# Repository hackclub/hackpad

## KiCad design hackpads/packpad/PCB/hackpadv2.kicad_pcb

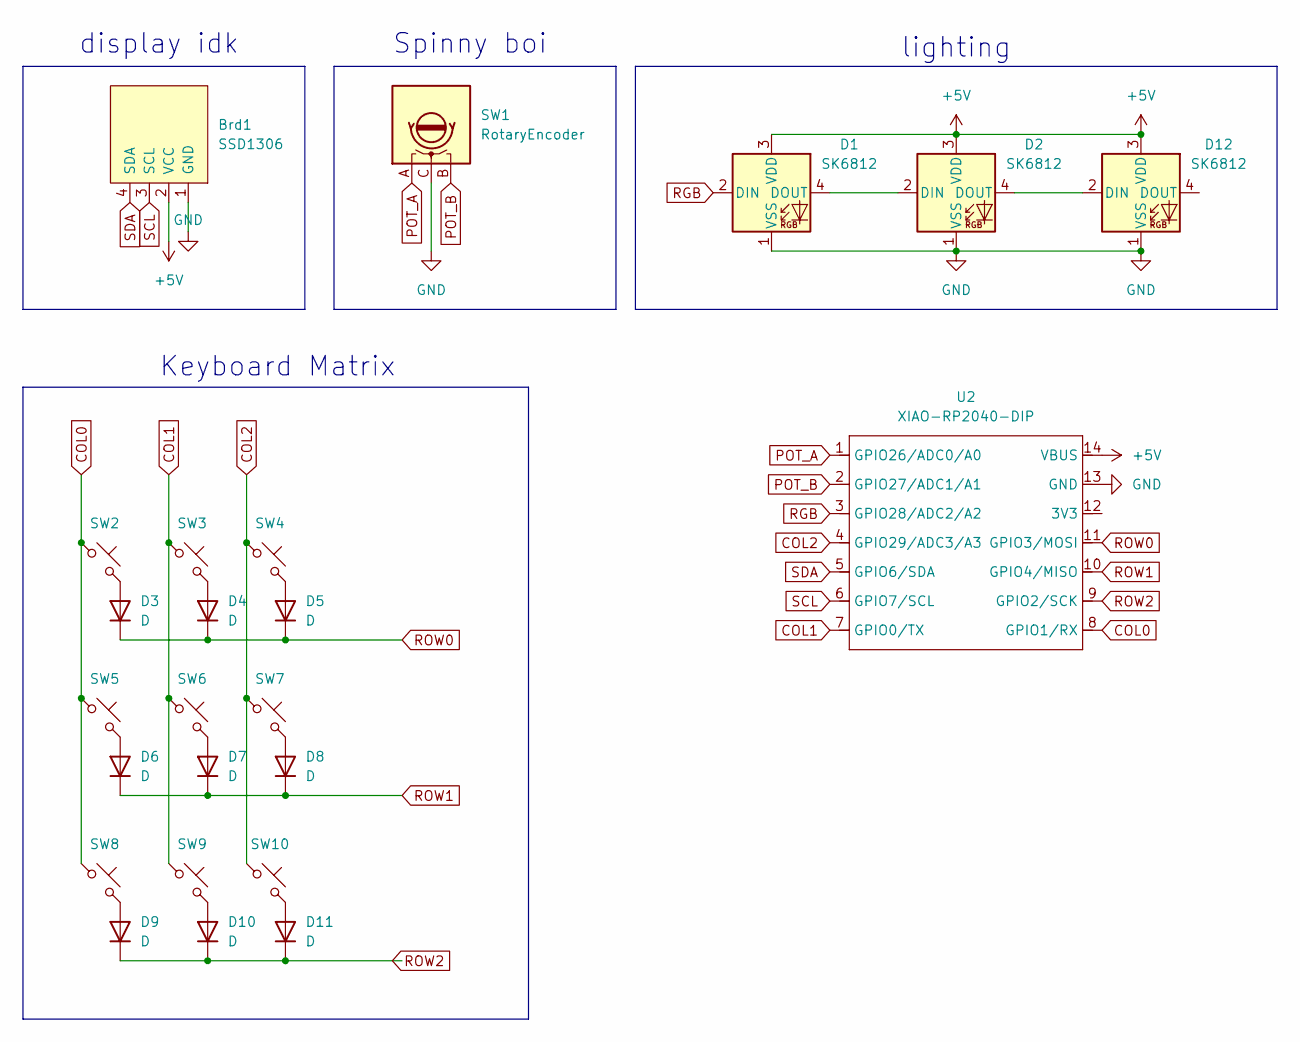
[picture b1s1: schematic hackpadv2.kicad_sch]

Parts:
Brd1: SSD1306
D1, D2, D12: SK6812; LED_SK6812_PLCC4_5.0x5.0mm_P3.2mm
D3, D4, D5, D6, D7, D8, D9, D10, D11: D; D_DO-35_SOD27_P7.62mm_Horizontal
SW1: RotaryEncoder; RotaryEncoder_Alps_EC11E-Switch_Vertical_H20mm
SW2, SW3, SW4, SW5, SW6, SW7, SW8, SW9, SW10: SW_Push_45deg; SW_Cherry_MX_1.00u_PCB
U2: XIAO-RP2040-DIP

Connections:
+5V: Brd1.2 (VCC), D1.3 (VDD), D2.3 (VDD), D12.3 (VDD), U2.14 (VBUS); also elsewhere on the board
COL0: SW2.1, SW5.1, SW8.1, U2.8 (GPIO1/RX)
COL1: SW3.1, SW6.1, SW9.1, U2.7 (GPIO0/TX)
COL2: SW4.1, SW7.1, SW10.1, U2.4 (GPIO29/ADC3/A3)
GND: Brd1.1 (GND), D1.1 (VSS), D2.1 (VSS), D12.1 (VSS), SW1.C, U2.13 (GND); also elsewhere on the board
unnamed: D1.4 (DOUT), D2.2 (DIN)
unnamed: D3.2 (A), SW2.2
unnamed: D4.2 (A), SW3.2
unnamed: D5.2 (A), SW4.2
unnamed: D6.2 (A), SW5.2
unnamed: D7.2 (A), SW6.2
unnamed: D8.2 (A), SW7.2
unnamed: D9.2 (A), SW8.2
unnamed: D10.2 (A), SW9.2
unnamed: D11.2 (A), SW10.2
unnamed: D2.4 (DOUT), D12.2 (DIN)
POT_A: SW1.A, U2.1 (GPIO26/ADC0/A0)
POT_B: SW1.B, U2.2 (GPIO27/ADC1/A1)
RGB: D1.2 (DIN), U2.3 (GPIO28/ADC2/A2)
ROW0: D3.1 (K), D4.1 (K), D5.1 (K), U2.11 (GPIO3/MOSI)
ROW1: D6.1 (K), D7.1 (K), D8.1 (K), U2.10 (GPIO4/MISO)
ROW2: D9.1 (K), D10.1 (K), D11.1 (K), U2.9 (GPIO2/SCK)
SCL: Brd1.3 (SCL), U2.6 (GPIO7/SCL); also elsewhere on the board
SDA: Brd1.4 (SDA), U2.5 (GPIO6/SDA); also elsewhere on the board

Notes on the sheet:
lighting
display idk
Keyboard Matrix
Spinny boi

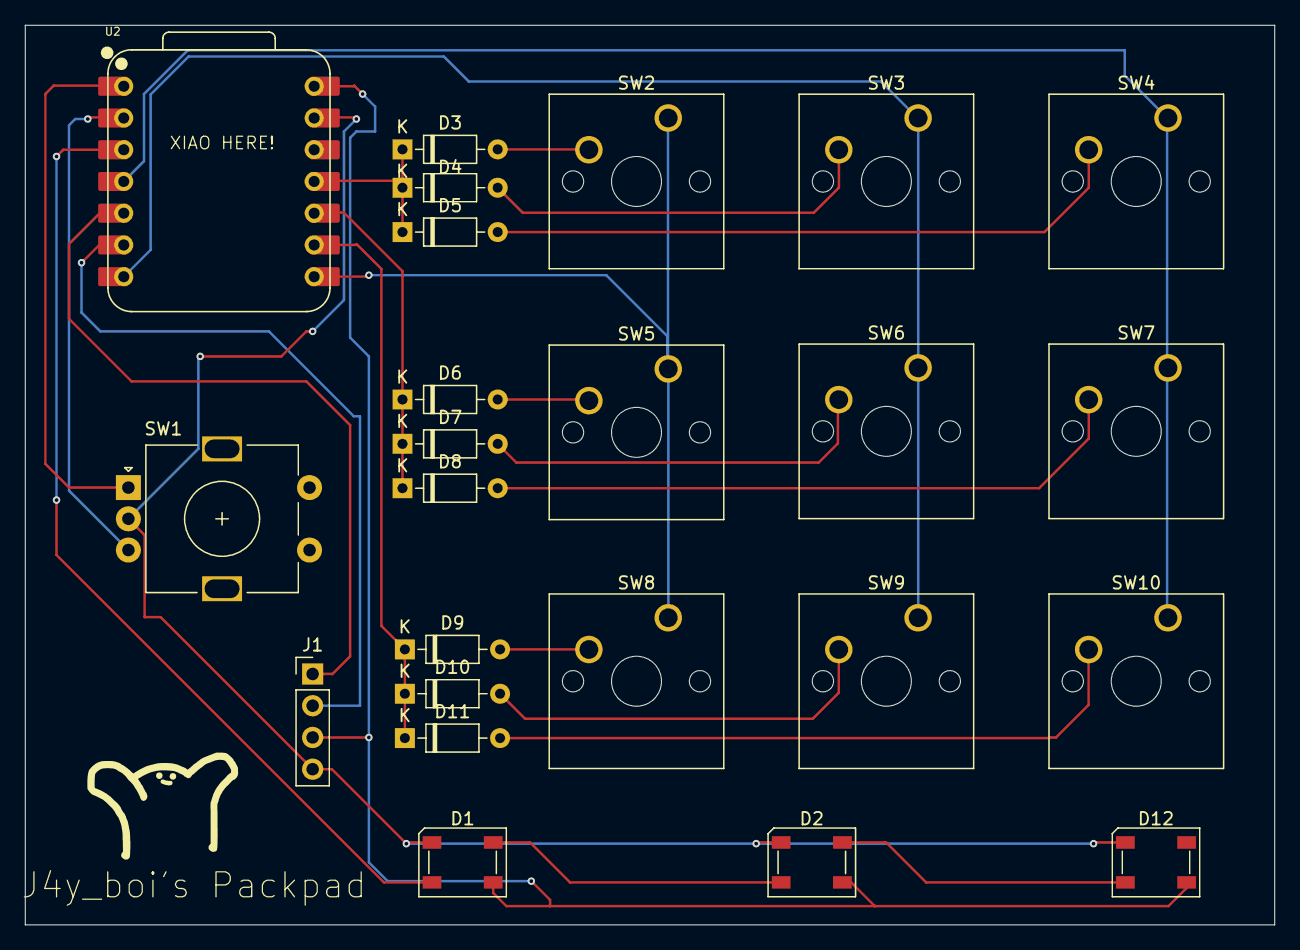
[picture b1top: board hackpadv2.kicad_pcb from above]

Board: 2 copper layers, 100.0 x 72.0 mm, 24 parts (0 on the bottom side), 24 nets.

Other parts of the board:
J1: OLED_DISPLAY; PinHeader_1x04_P2.54mm_Vertical

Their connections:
+5V: J1.3; also elsewhere on the board
GND: J1.4; also elsewhere on the board
SCL: J1.2; also elsewhere on the board
SDA: J1.1; also elsewhere on the board

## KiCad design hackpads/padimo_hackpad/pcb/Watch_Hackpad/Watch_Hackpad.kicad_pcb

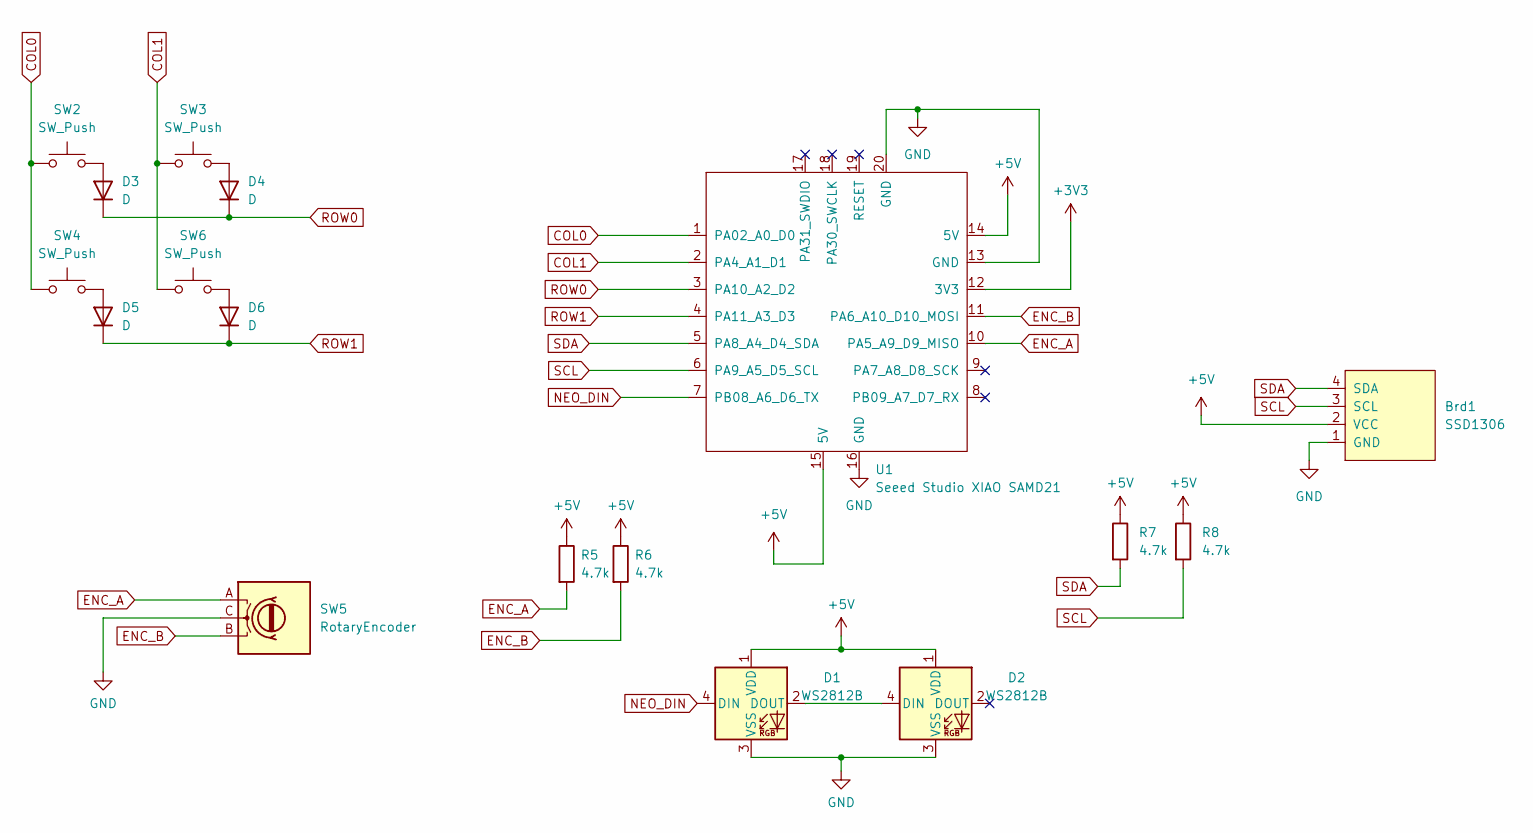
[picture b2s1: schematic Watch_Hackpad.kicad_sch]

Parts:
Brd1: SSD1306; SSD1306_128x64
D1, D2: WS2812B; LED_WS2812B_PLCC4_5.0x5.0mm_P3.2mm
D3, D4, D5, D6: D; D_DO-35_SOD27_P7.62mm_Horizontal
R5, R6, R7, R8: 4.7k; CF14JT4K70
SW2, SW3, SW4, SW6: SW_Push; SW_Cherry_MX_1.00u_PCB
SW5: RotaryEncoder; RotaryEncoder_Alps_EC11E-Switch_Vertical_H20mm
U1: Seeed Studio XIAO SAMD21; XIAO-SAMD21-RP2040-14P-2.54-21X17.8MM (Seeeduino XIAO)

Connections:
+3V3: U1.12 (3V3)
+5V: Brd1.2 (VCC), D1.1 (VDD), D2.1 (VDD), R5.1, R6.1, R7.1, R8.1, U1.14 (5V), U1.15 (5V)
COL0: SW2.1, SW4.1, U1.1 (PA02_A0_D0)
COL1: SW3.1, SW6.1, U1.2 (PA4_A1_D1)
ENC_A: R5.2, SW5.A, U1.10 (PA5_A9_D9_MISO)
ENC_B: R6.2, SW5.B, U1.11 (PA6_A10_D10_MOSI)
GND: Brd1.1 (GND), D1.3 (VSS), D2.3 (VSS), SW5.C, U1.13 (GND), U1.16 (GND), U1.20 (GND)
NEO_DIN: D1.4 (DIN), U1.7 (PB08_A6_D6_TX)
unnamed: D1.2 (DOUT), D2.4 (DIN)
unnamed: D3.2 (A), SW2.2
unnamed: D4.2 (A), SW3.2
unnamed: D5.2 (A), SW4.2
unnamed: D6.2 (A), SW6.2
ROW0: D3.1 (K), D4.1 (K), U1.3 (PA10_A2_D2)
ROW1: D5.1 (K), D6.1 (K), U1.4 (PA11_A3_D3)
SCL: Brd1.3 (SCL), R8.2, U1.6 (PA9_A5_D5_SCL)
SDA: Brd1.4 (SDA), R7.2, U1.5 (PA8_A4_D4_SDA)

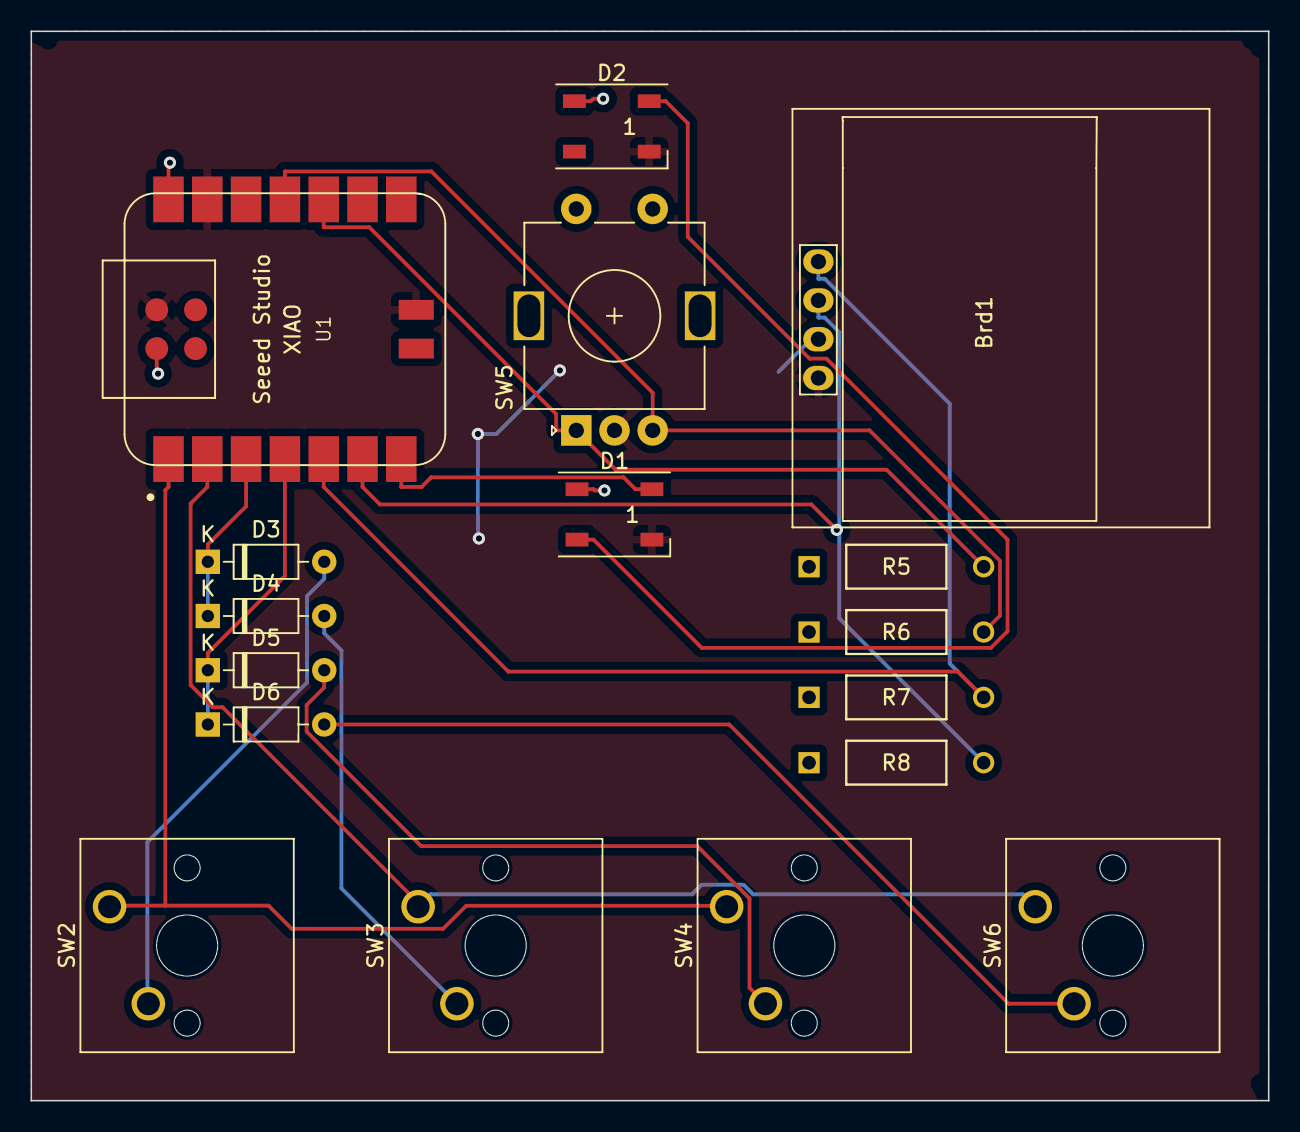
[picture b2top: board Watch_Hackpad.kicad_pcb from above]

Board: 2 copper layers, 81.0 x 70.0 mm, 17 parts (0 on the bottom side), 16 nets.

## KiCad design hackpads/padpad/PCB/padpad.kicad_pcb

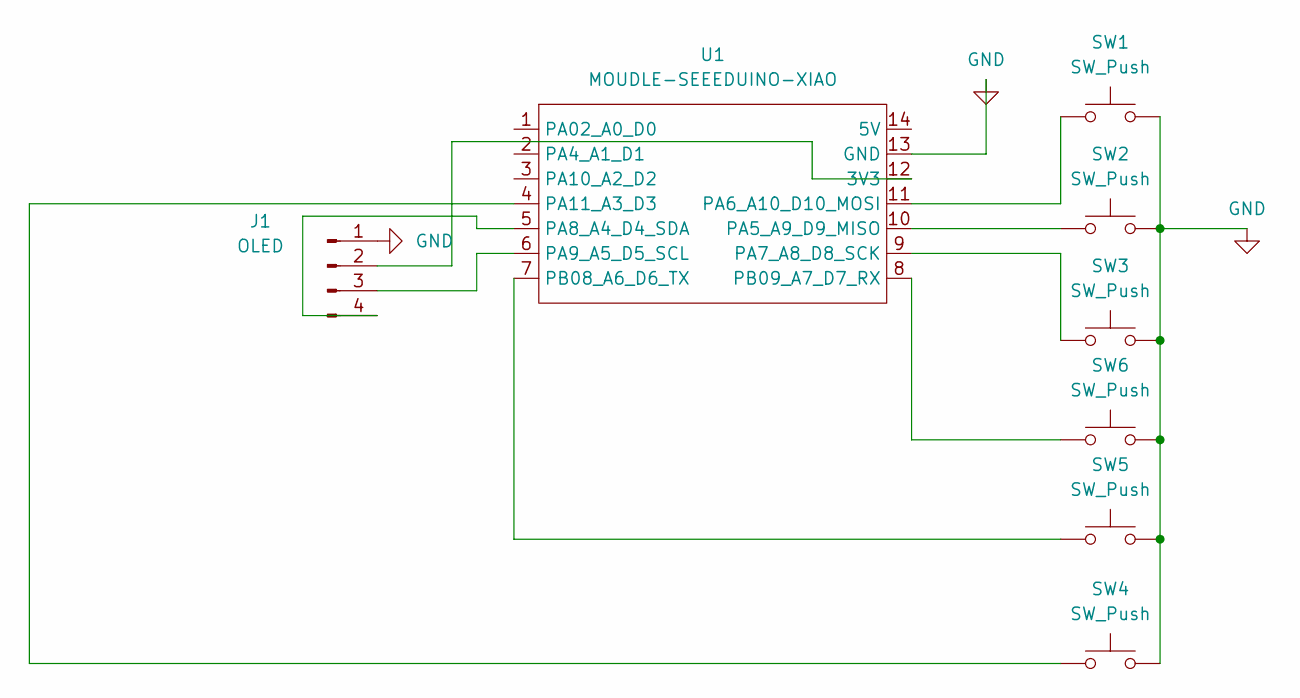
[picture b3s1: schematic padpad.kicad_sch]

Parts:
J1: OLED; SSD1306-0.91-OLED-4pin-128x32
SW1, SW2, SW3, SW4, SW5, SW6: SW_Push; SW_Cherry_MX_1.00u_PCB
U1: MOUDLE-SEEEDUINO-XIAO; XIAO-Generic-Hybrid-14P-2.54-21X17.8MM

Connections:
GND: J1.1, SW1.2, SW2.2, SW3.2, SW4.2, SW5.2, SW6.2, U1.13 (GND)
unnamed: J1.2, U1.12 (3V3)
unnamed: J1.3, U1.6 (PA9_A5_D5_SCL)
unnamed: J1.4, U1.5 (PA8_A4_D4_SDA)
unnamed: SW2.1, U1.10 (PA5_A9_D9_MISO)
unnamed: SW1.1, U1.11 (PA6_A10_D10_MOSI)
unnamed: SW3.1, U1.9 (PA7_A8_D8_SCK)
unnamed: SW4.1, U1.4 (PA11_A3_D3)
unnamed: SW5.1, U1.7 (PB08_A6_D6_TX)
unnamed: SW6.1, U1.8 (PB09_A7_D7_RX)

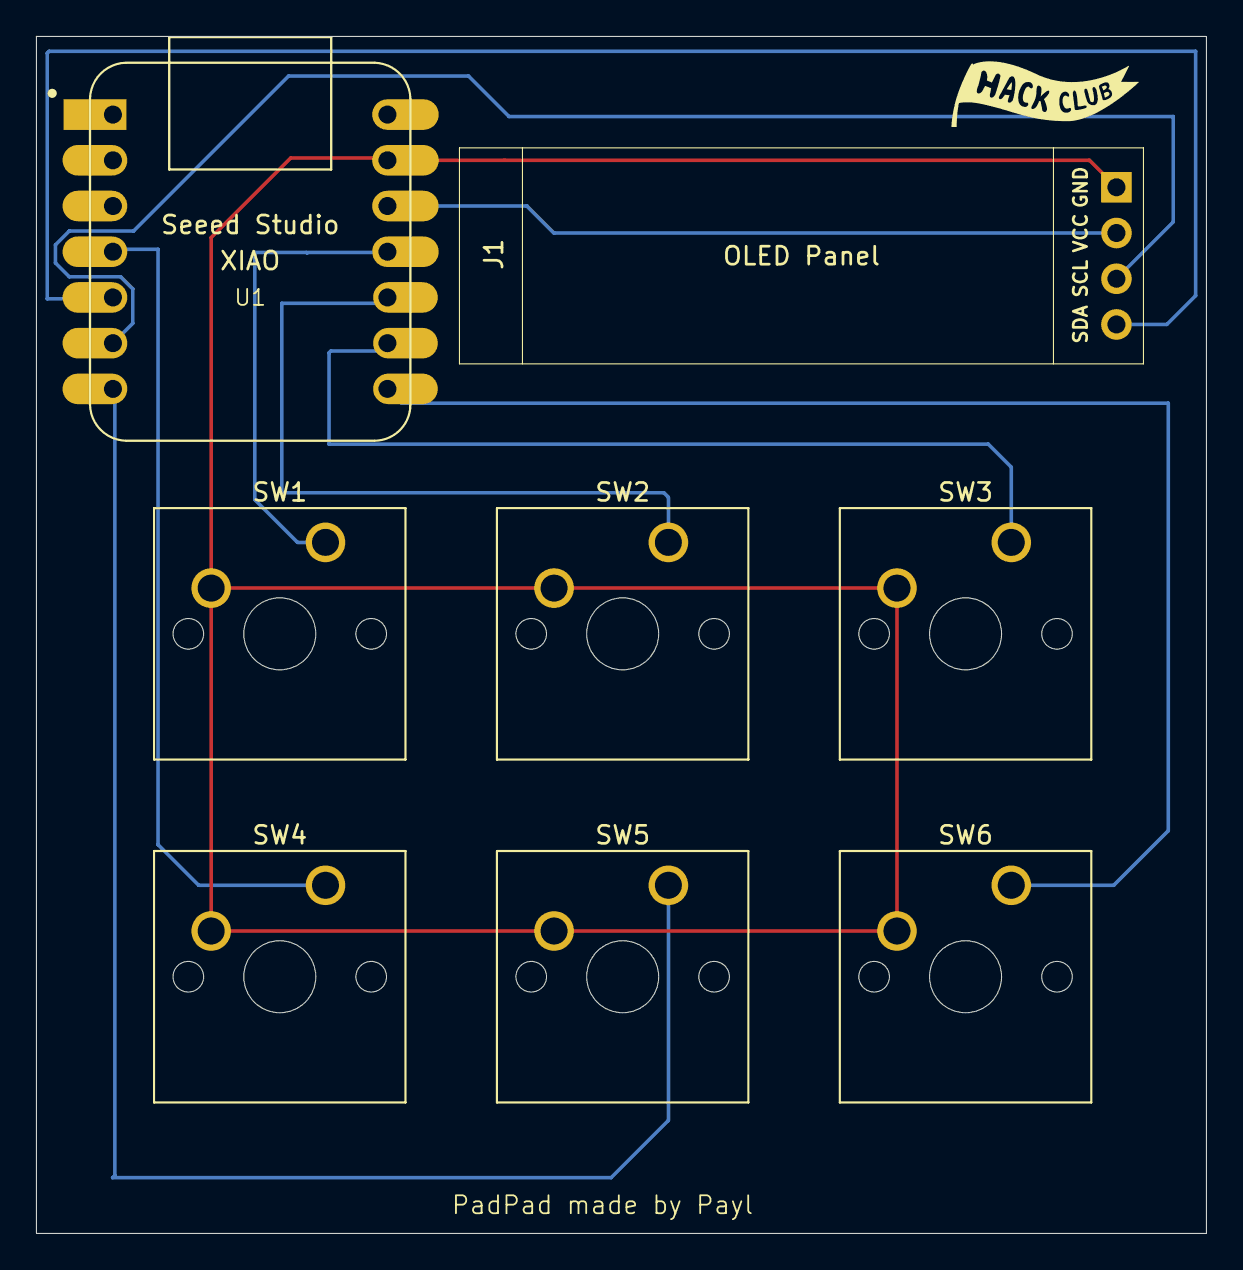
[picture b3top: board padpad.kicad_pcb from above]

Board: 2 copper layers, 65.0 x 66.5 mm, 8 parts (0 on the bottom side), 10 nets.

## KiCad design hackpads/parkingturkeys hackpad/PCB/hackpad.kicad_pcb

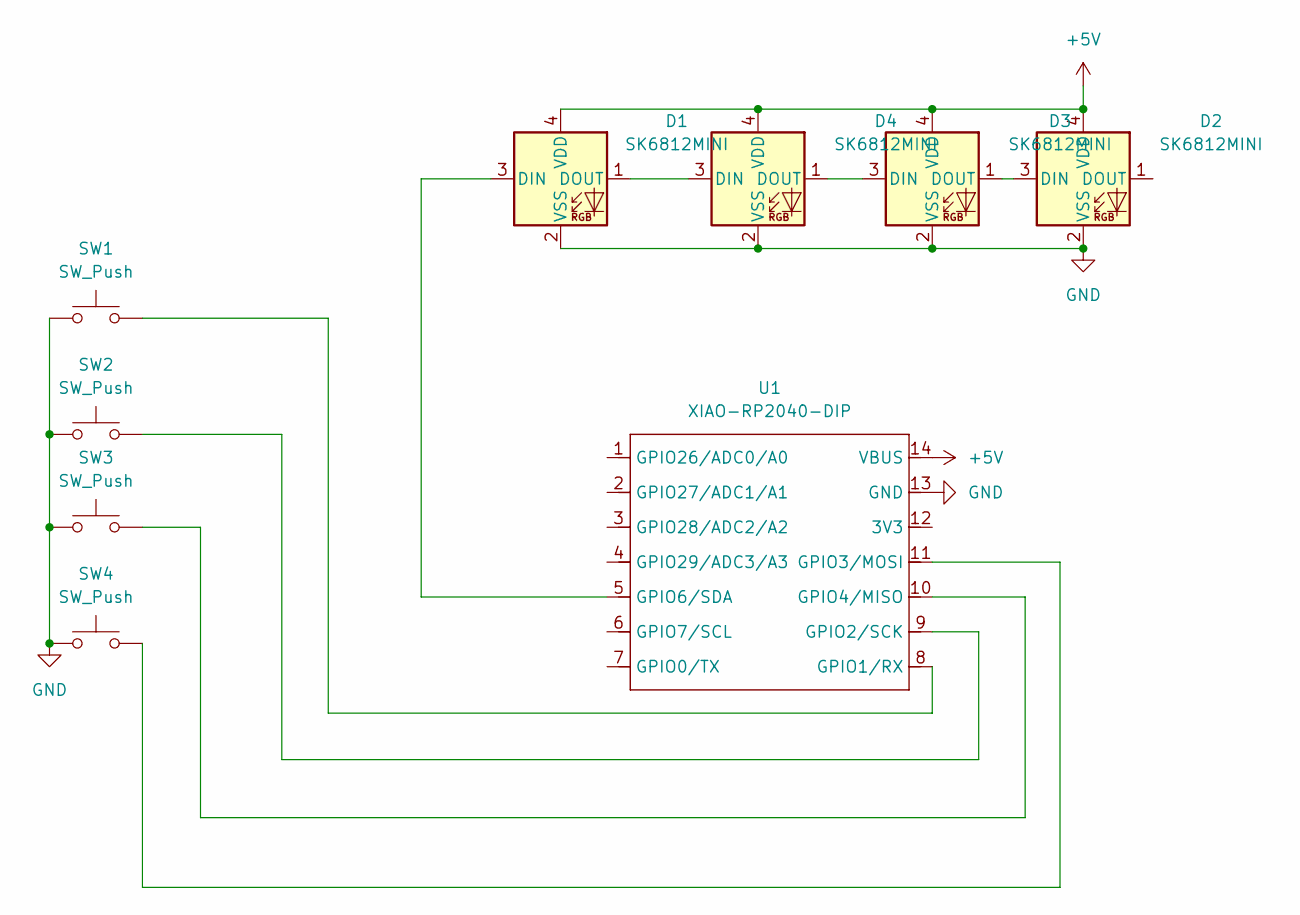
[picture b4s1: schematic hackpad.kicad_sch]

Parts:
D1, D2, D3, D4: SK6812MINI; LED_SK6812MINI_PLCC4_3.5x3.5mm_P1.75mm
SW1, SW2, SW3, SW4: SW_Push; SW_Cherry_MX_1.00u_PCB
U1: XIAO-RP2040-DIP

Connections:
+5V: D1.4 (VDD), D2.4 (VDD), D3.4 (VDD), D4.4 (VDD), U1.14 (VBUS)
GND: D1.2 (VSS), D2.2 (VSS), D3.2 (VSS), D4.2 (VSS), SW1.1, SW2.1, SW3.1, SW4.1, U1.13 (GND)
unnamed: D1.3 (DIN), U1.5 (GPIO6/SDA)
unnamed: D1.1 (DOUT), D4.3 (DIN)
unnamed: D2.3 (DIN), D3.1 (DOUT)
unnamed: D3.3 (DIN), D4.1 (DOUT)
unnamed: SW1.2, U1.8 (GPIO1/RX)
unnamed: SW2.2, U1.9 (GPIO2/SCK)
unnamed: SW4.2, U1.11 (GPIO3/MOSI)
unnamed: SW3.2, U1.10 (GPIO4/MISO)

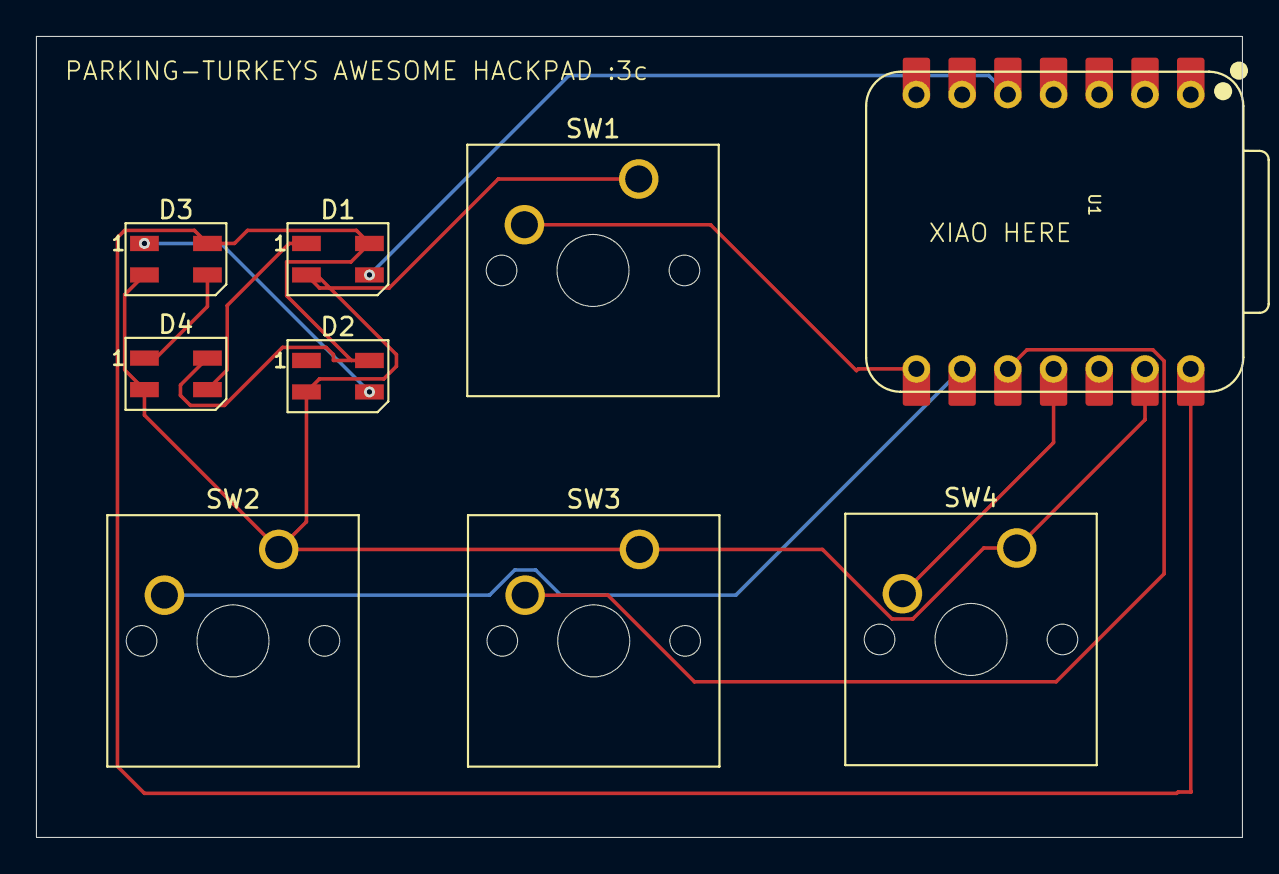
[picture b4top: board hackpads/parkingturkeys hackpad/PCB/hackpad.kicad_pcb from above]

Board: 2 copper layers, 67.0 x 44.5 mm, 9 parts (0 on the bottom side), 10 nets.

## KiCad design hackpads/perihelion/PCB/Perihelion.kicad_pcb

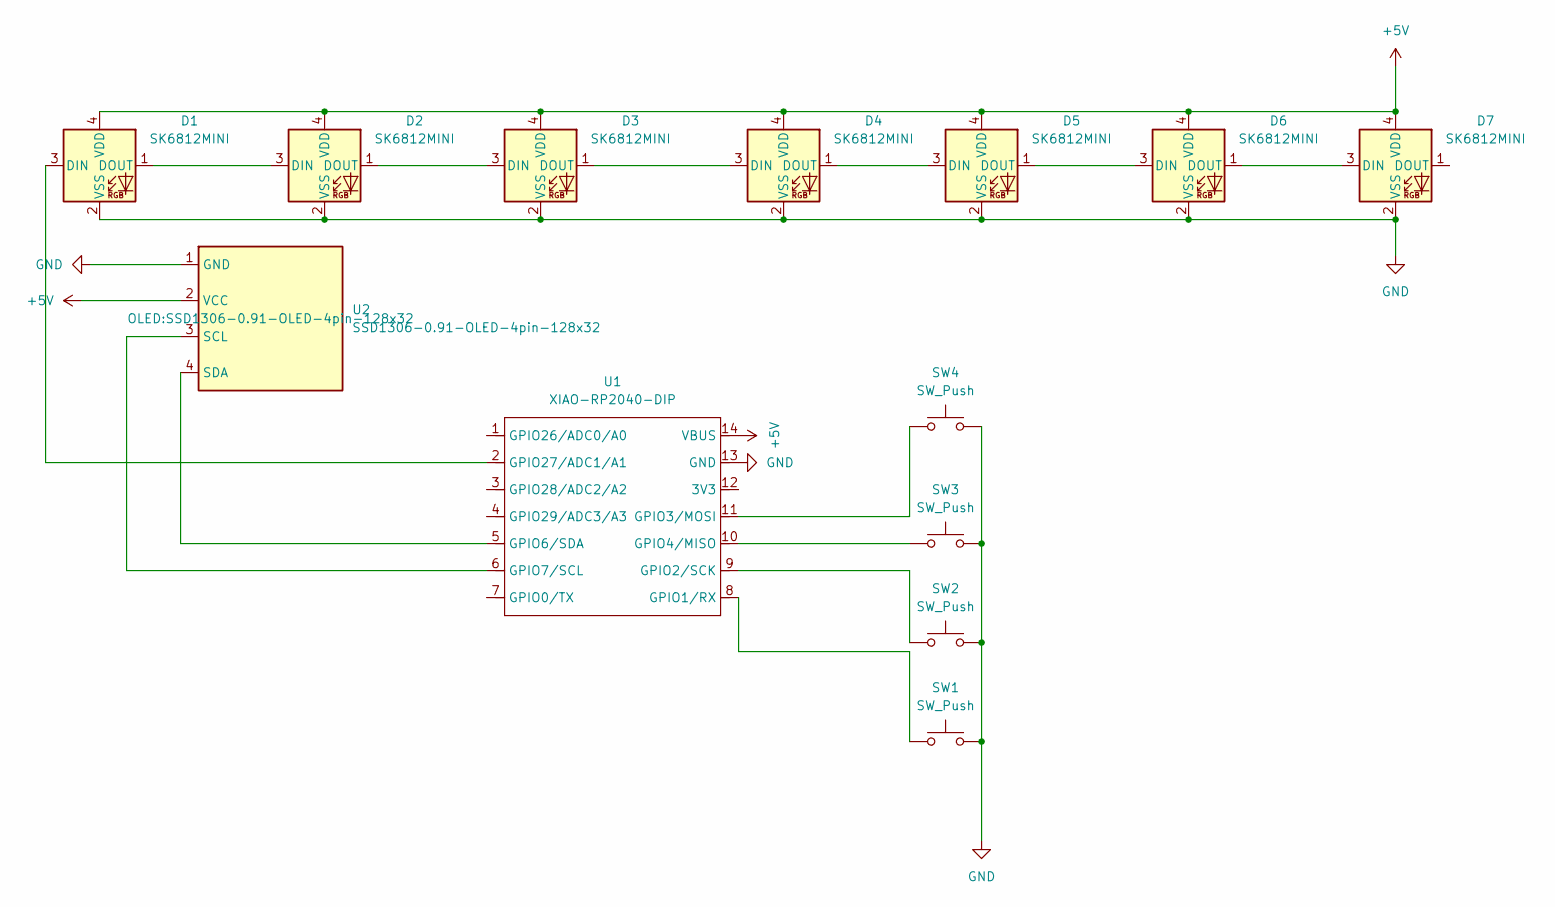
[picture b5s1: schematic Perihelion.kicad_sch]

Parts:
D1, D2, D3, D4, D5, D6, D7: SK6812MINI; LED_SK6812MINI_PLCC4_3.5x3.5mm_P1.75mm
SW1, SW2, SW3, SW4: SW_Push; SW_Cherry_MX_1.00u_PCB
U1: XIAO-RP2040-DIP
U2: SSD1306-0.91-OLED-4pin-128x32

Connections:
+5V: D1.4 (VDD), D2.4 (VDD), D3.4 (VDD), D4.4 (VDD), D5.4 (VDD), D6.4 (VDD), D7.4 (VDD), U1.14 (VBUS), U2.2 (VCC)
GND: D1.2 (VSS), D2.2 (VSS), D3.2 (VSS), D4.2 (VSS), D5.2 (VSS), D6.2 (VSS), D7.2 (VSS), SW1.2, SW2.2, SW3.2, SW4.2, U1.13 (GND), U2.1 (GND)
unnamed: D1.3 (DIN), U1.2 (GPIO27/ADC1/A1)
unnamed: D1.1 (DOUT), D2.3 (DIN)
unnamed: D2.1 (DOUT), D3.3 (DIN)
unnamed: D3.1 (DOUT), D4.3 (DIN)
unnamed: D4.1 (DOUT), D5.3 (DIN)
unnamed: D5.1 (DOUT), D6.3 (DIN)
unnamed: D6.1 (DOUT), D7.3 (DIN)
unnamed: SW1.1, U1.8 (GPIO1/RX)
unnamed: SW2.1, U1.9 (GPIO2/SCK)
unnamed: SW4.1, U1.11 (GPIO3/MOSI)
unnamed: SW3.1, U1.10 (GPIO4/MISO)
unnamed: U1.5 (GPIO6/SDA), U2.4 (SDA)
unnamed: U1.6 (GPIO7/SCL), U2.3 (SCL)

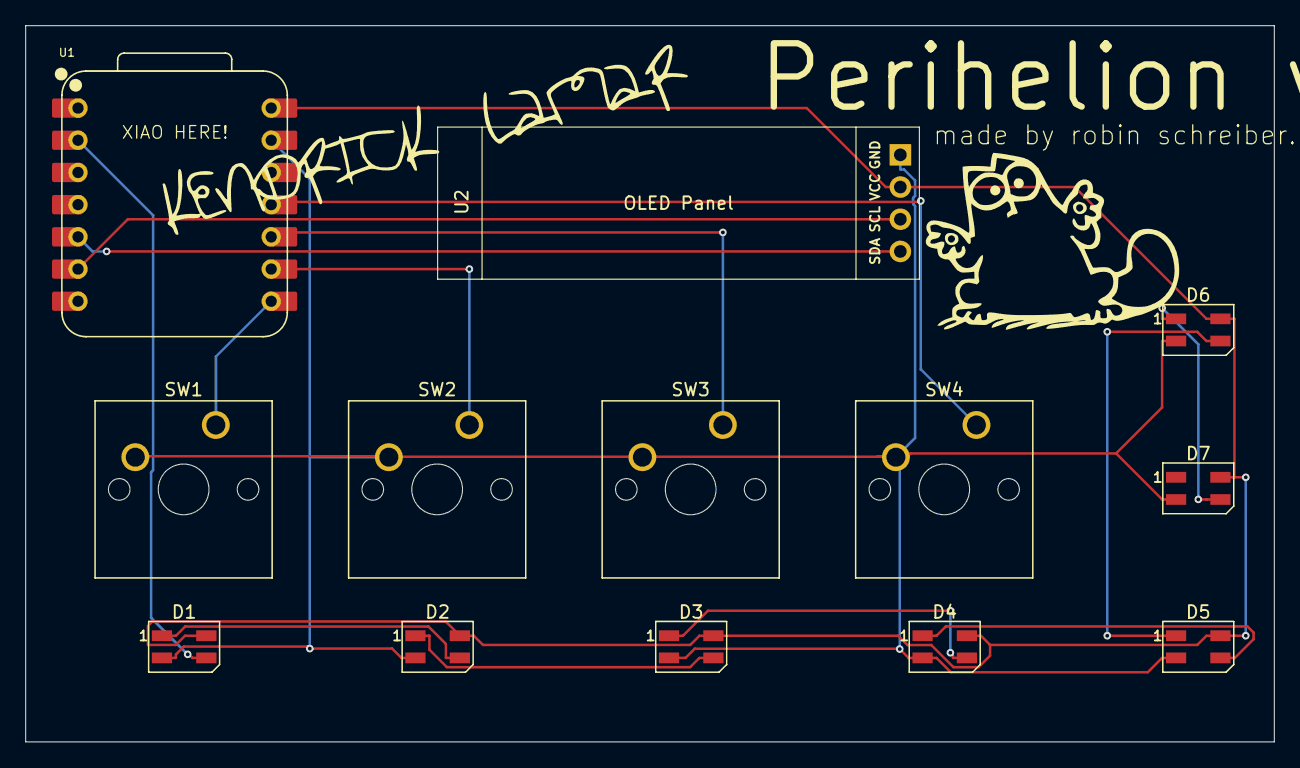
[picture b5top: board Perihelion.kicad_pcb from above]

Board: 2 copper layers, 98.5 x 56.5 mm, 13 parts (0 on the bottom side), 15 nets.

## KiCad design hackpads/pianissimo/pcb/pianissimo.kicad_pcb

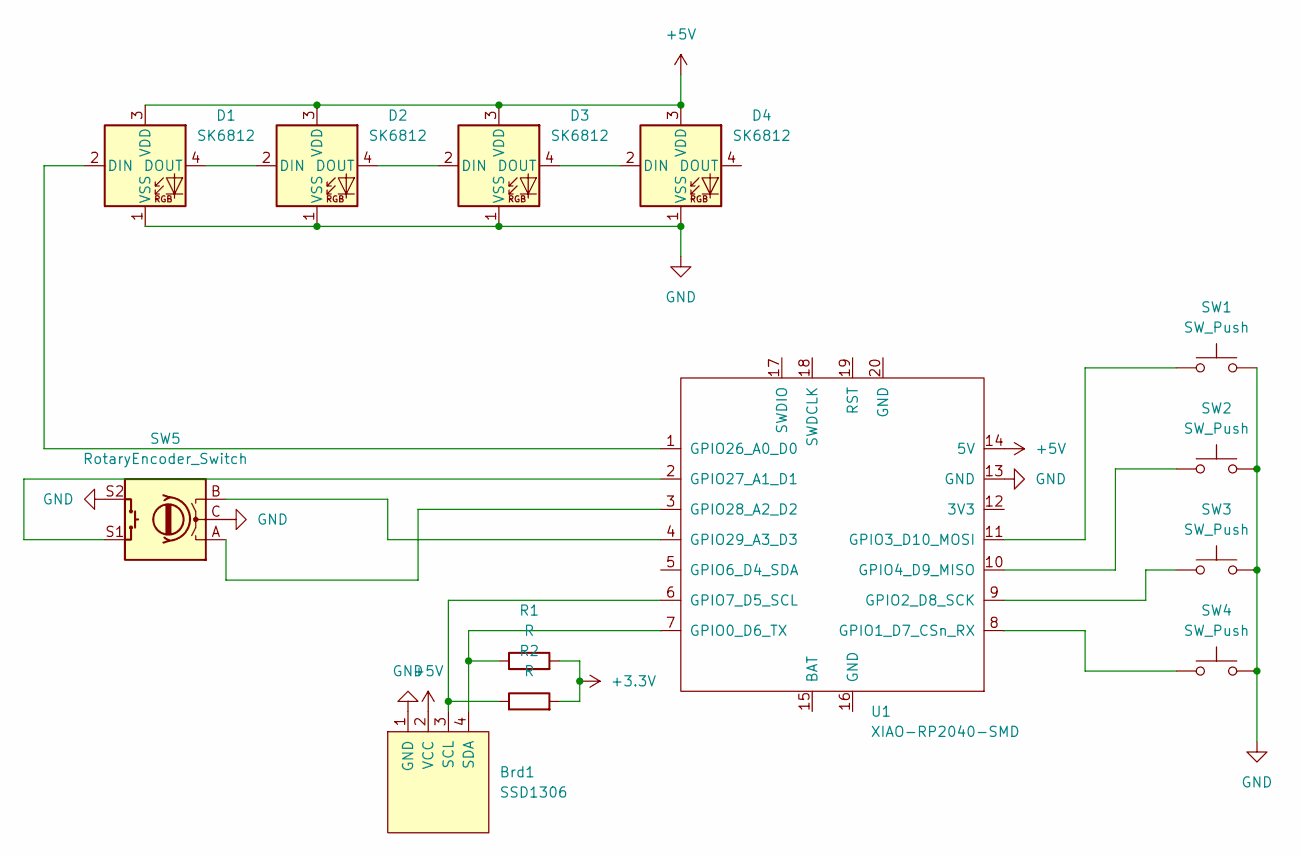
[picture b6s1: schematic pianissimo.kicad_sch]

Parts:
Brd1: SSD1306; 128x64OLED
D1, D2, D3, D4: SK6812; LED_SK6812MINI_PLCC4_3.5x3.5mm_P1.75mm
R1, R2: R; Resistor
SW1, SW2, SW3, SW4: SW_Push; SW_Cherry_MX1A_1.00u_PCB
SW5: RotaryEncoder_Switch; RotaryEncoder_Alps_EC11E-Switch_Vertical_H20mm_CircularMoun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
U1: XIAO-RP2040-SMD; XIAO-RP2040-DIP

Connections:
+3.3V: R1.2, R2.2
+5V: Brd1.2 (VCC), D1.3 (VDD), D2.3 (VDD), D3.3 (VDD), D4.3 (VDD), U1.14 (5V)
GND: Brd1.1 (GND), D1.1 (VSS), D2.1 (VSS), D3.1 (VSS), D4.1 (VSS), SW1.2, SW2.2, SW3.2, SW4.2, SW5.C, SW5.S2, U1.13 (GND)
unnamed: Brd1.3 (SCL), R2.1, U1.6 (GPIO7_D5_SCL)
unnamed: Brd1.4 (SDA), R1.1, U1.7 (GPIO0_D6_TX)
unnamed: D1.2 (DIN), U1.1 (GPIO26_A0_D0)
unnamed: D1.4 (DOUT), D2.2 (DIN)
unnamed: D2.4 (DOUT), D3.2 (DIN)
unnamed: D3.4 (DOUT), D4.2 (DIN)
unnamed: SW4.1, U1.8 (GPIO1_D7_CSn_RX)
unnamed: SW3.1, U1.9 (GPIO2_D8_SCK)
unnamed: SW1.1, U1.11 (GPIO3_D10_MOSI)
unnamed: SW2.1, U1.10 (GPIO4_D9_MISO)
unnamed: SW5.S1, U1.2 (GPIO27_A1_D1)
unnamed: SW5.A, U1.3 (GPIO28_A2_D2)
unnamed: SW5.B, U1.4 (GPIO29_A3_D3)

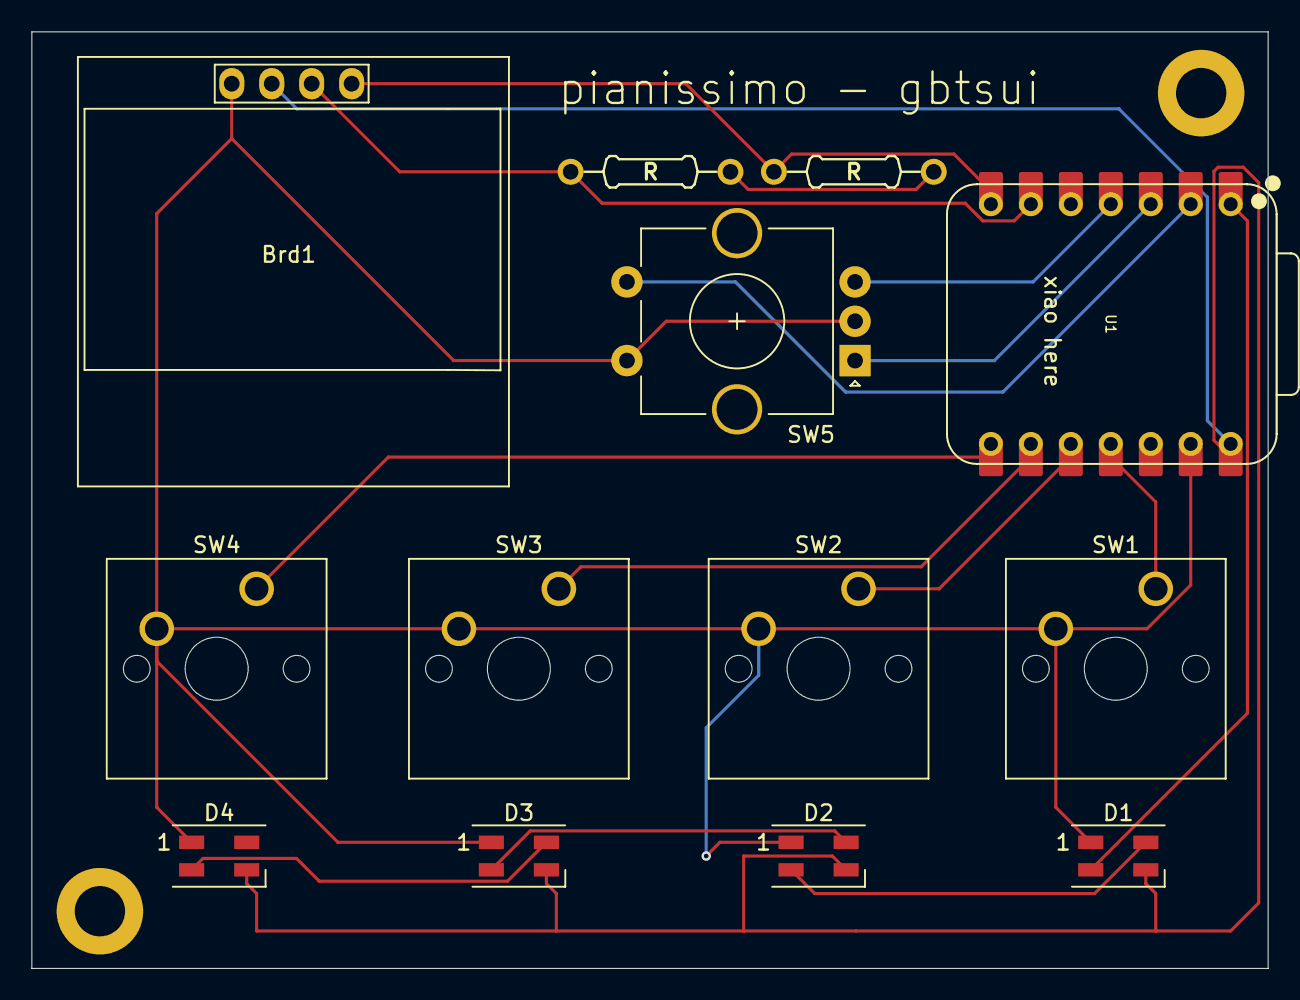
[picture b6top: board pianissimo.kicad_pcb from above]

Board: 2 copper layers, 78.6 x 59.5 mm, 13 parts (0 on the bottom side), 16 nets.

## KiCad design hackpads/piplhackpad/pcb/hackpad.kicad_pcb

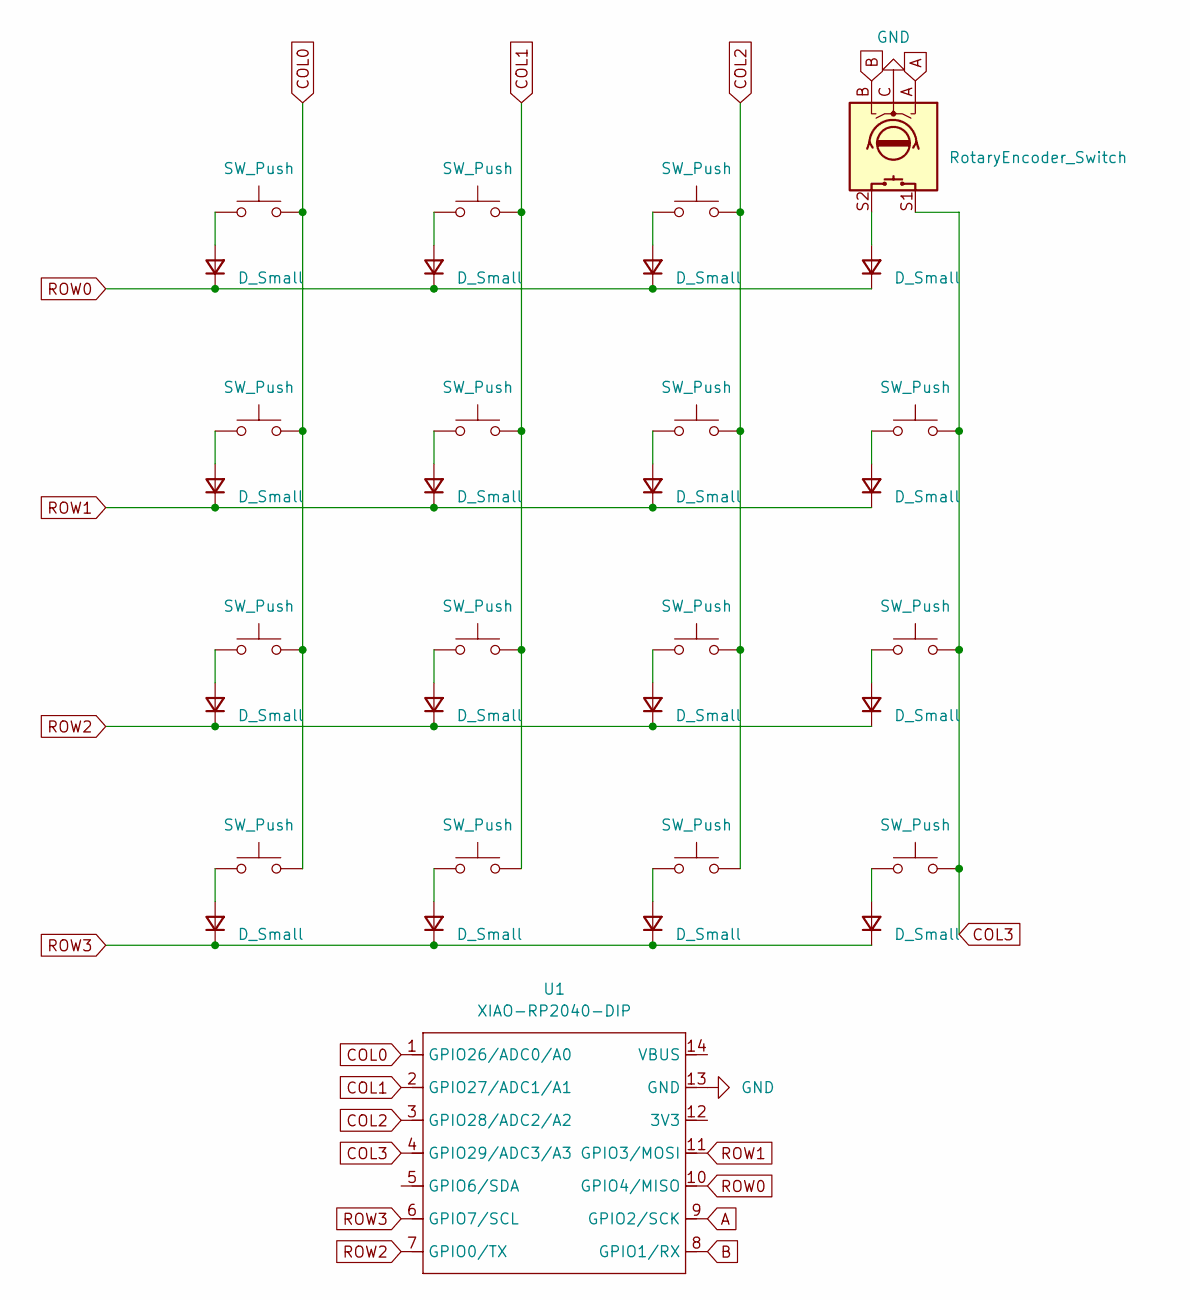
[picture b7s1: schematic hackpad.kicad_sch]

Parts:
D1, D2, D3, D4, D5, D6, D7, D8, D9, D10, D11, D12, D13, D14, D15, D16: D_Small; D_DO-35_SOD27_P7.62mm_Horizontal
SW1, SW2, SW3, SW4, SW5, SW6, SW7, SW8, SW9, SW11, SW12, SW13, SW14, SW15, SW16: SW_Push; SW_Cherry_MX_1.00u_PCB
SW10: RotaryEncoder_Switch; RotaryEncoder_Alps_EC11E-Switch_Vertical_H20mm
U1: XIAO-RP2040-DIP

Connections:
A: SW10.A, U1.9 (GPIO2/SCK)
B: SW10.B, U1.8 (GPIO1/RX)
COL0: SW1.2, SW2.2, SW8.2, SW13.2, U1.1 (GPIO26/ADC0/A0)
COL1: SW3.2, SW4.2, SW9.2, SW14.2, U1.2 (GPIO27/ADC1/A1)
COL2: SW5.2, SW7.2, SW11.2, SW15.2, U1.3 (GPIO28/ADC2/A2)
COL3: SW6.2, SW10.S1, SW12.2, SW16.2, U1.4 (GPIO29/ADC3/A3)
GND: SW10.C, U1.13 (GND)
unnamed: D1.2 (A), SW1.1
unnamed: D2.2 (A), SW4.1
unnamed: D3.2 (A), SW7.1
unnamed: D4.2 (A), SW10.S2
unnamed: D5.2 (A), SW2.1
unnamed: D6.2 (A), SW3.1
unnamed: D7.2 (A), SW5.1
unnamed: D8.2 (A), SW6.1
unnamed: D9.2 (A), SW8.1
unnamed: D10.2 (A), SW9.1
unnamed: D11.2 (A), SW11.1
unnamed: D12.2 (A), SW12.1
unnamed: D13.2 (A), SW13.1
unnamed: D14.2 (A), SW14.1
unnamed: D15.2 (A), SW15.1
unnamed: D16.2 (A), SW16.1
ROW0: D1.1 (K), D2.1 (K), D3.1 (K), D4.1 (K), U1.10 (GPIO4/MISO)
ROW1: D5.1 (K), D6.1 (K), D7.1 (K), D8.1 (K), U1.11 (GPIO3/MOSI)
ROW2: D9.1 (K), D10.1 (K), D11.1 (K), D12.1 (K), U1.7 (GPIO0/TX)
ROW3: D13.1 (K), D14.1 (K), D15.1 (K), D16.1 (K), U1.6 (GPIO7/SCL)

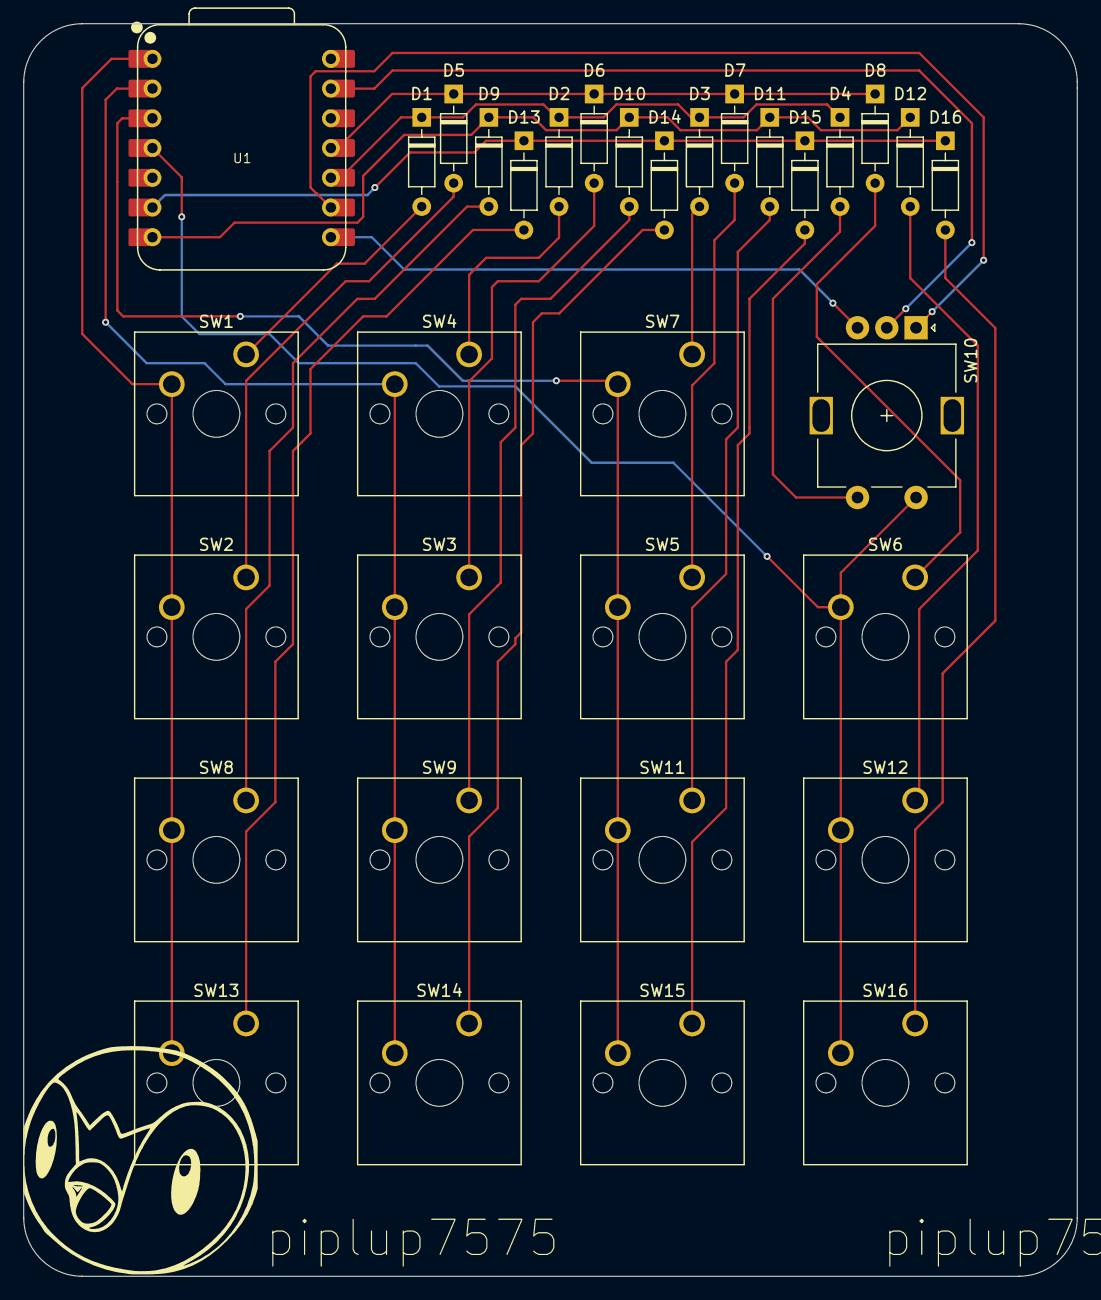
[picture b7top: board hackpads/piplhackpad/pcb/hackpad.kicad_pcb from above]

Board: 2 copper layers, 90.0 x 107.0 mm, 33 parts (0 on the bottom side), 27 nets.
